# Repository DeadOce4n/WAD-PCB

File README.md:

# WearableAffectionDevice - Circuito Impreso

En este repositorio se encuentra el esquemático y el diseño de PCB para el circuito impreso
del "Dispositivo Vestible para la Transmisión de Muestras de Afecto entre Familiares Separados
Geográficamente". Desarrollado en Autodesk EAGLE.

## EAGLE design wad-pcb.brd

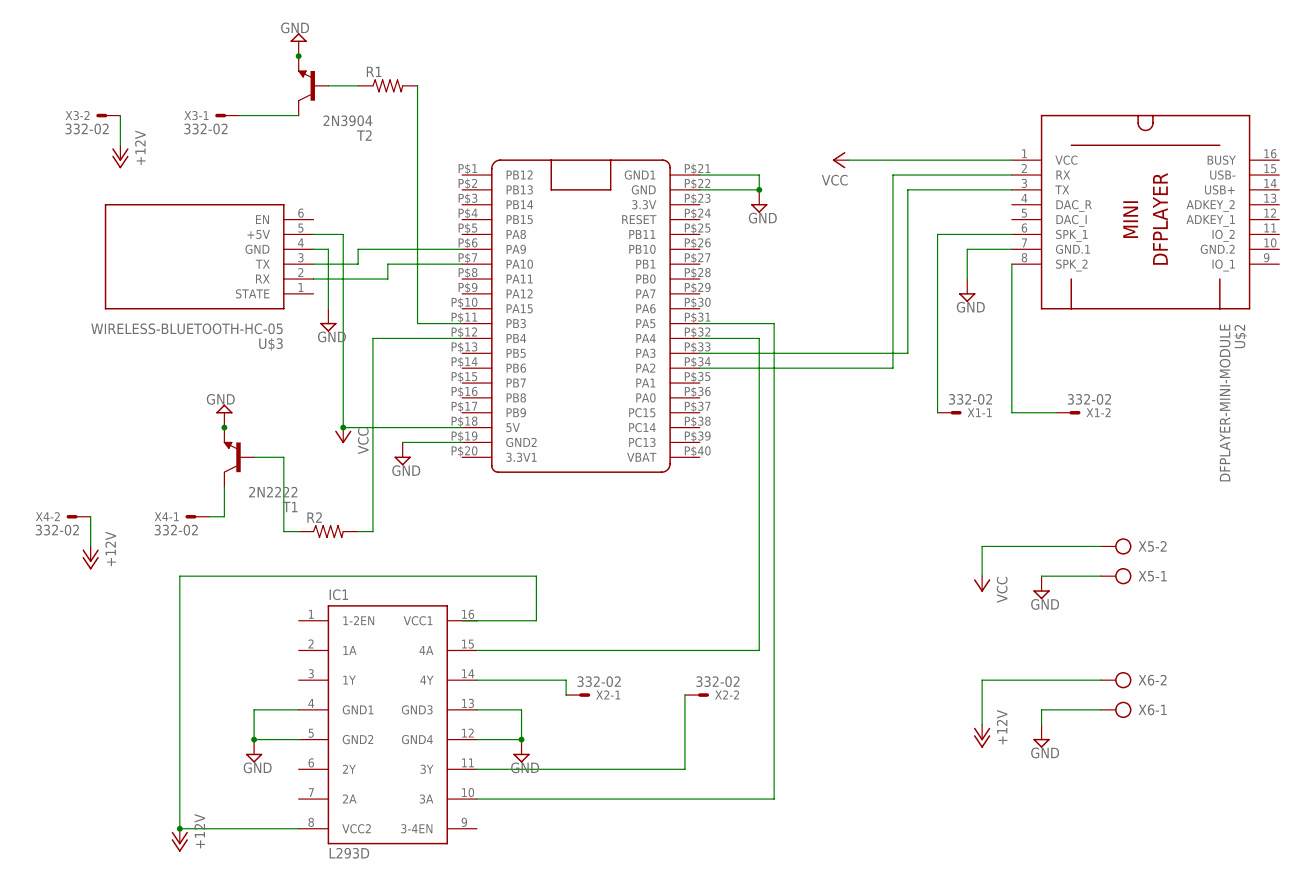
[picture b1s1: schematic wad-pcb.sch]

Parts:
IC1: L293D; DIL16
R1, R2: R-US_0204/7; 0204/7
T1: 2N2222; TO18
T2: 2N3904; TO92
U$1: BLUE_PILL
U$2: DFPLAYER-MINI-MODULE
U$3: WIRELESS-BLUETOOTH-HC-05
X1, X2, X3, X4: 332-02
X5, X6: AK500/2-H

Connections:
+12V: IC1.8 (VCC2), IC1.16 (VCC1), X3.2, X4.2, X6.2
GND: IC1.4 (GND1), IC1.5 (GND2), IC1.12 (GND4), IC1.13 (GND3), T1.1 (E), T2.3 (E), U$1.P$19 (GND2), U$1.P$21 (GND1), U$1.P$22 (GND), U$2.7 (GND.1), U$3.4 (GND), X5.1, X6.1
GND.2: U$2.10 (GND.2)
unnamed: U$1.P$6 (PA9), U$3.3 (TX)
unnamed: U$1.P$7 (PA10), U$3.2 (RX)
unnamed: R1.1, T2.2 (B)
unnamed: R1.2, U$1.P$11 (PB3)
unnamed: R2.1, T1.2 (B)
unnamed: R2.2, U$1.P$12 (PB4)
unnamed: T2.1 (C), X3.1
unnamed: T1.3 (C), X4.1
unnamed: U$1.P$34 (PA2), U$2.2 (RX)
unnamed: U$1.P$33 (PA3), U$2.3 (TX)
unnamed: U$2.6 (SPK_1), X1.1
unnamed: U$2.8 (SPK_2), X1.2
unnamed: IC1.15 (4A), U$1.P$32 (PA4)
unnamed: IC1.10 (3A), U$1.P$31 (PA5)
unnamed: IC1.14 (4Y), X2.1
unnamed: IC1.11 (3Y), X2.2
VCC: U$1.P$18 (5V), U$2.1 (VCC), U$3.5 (+5V), X5.2

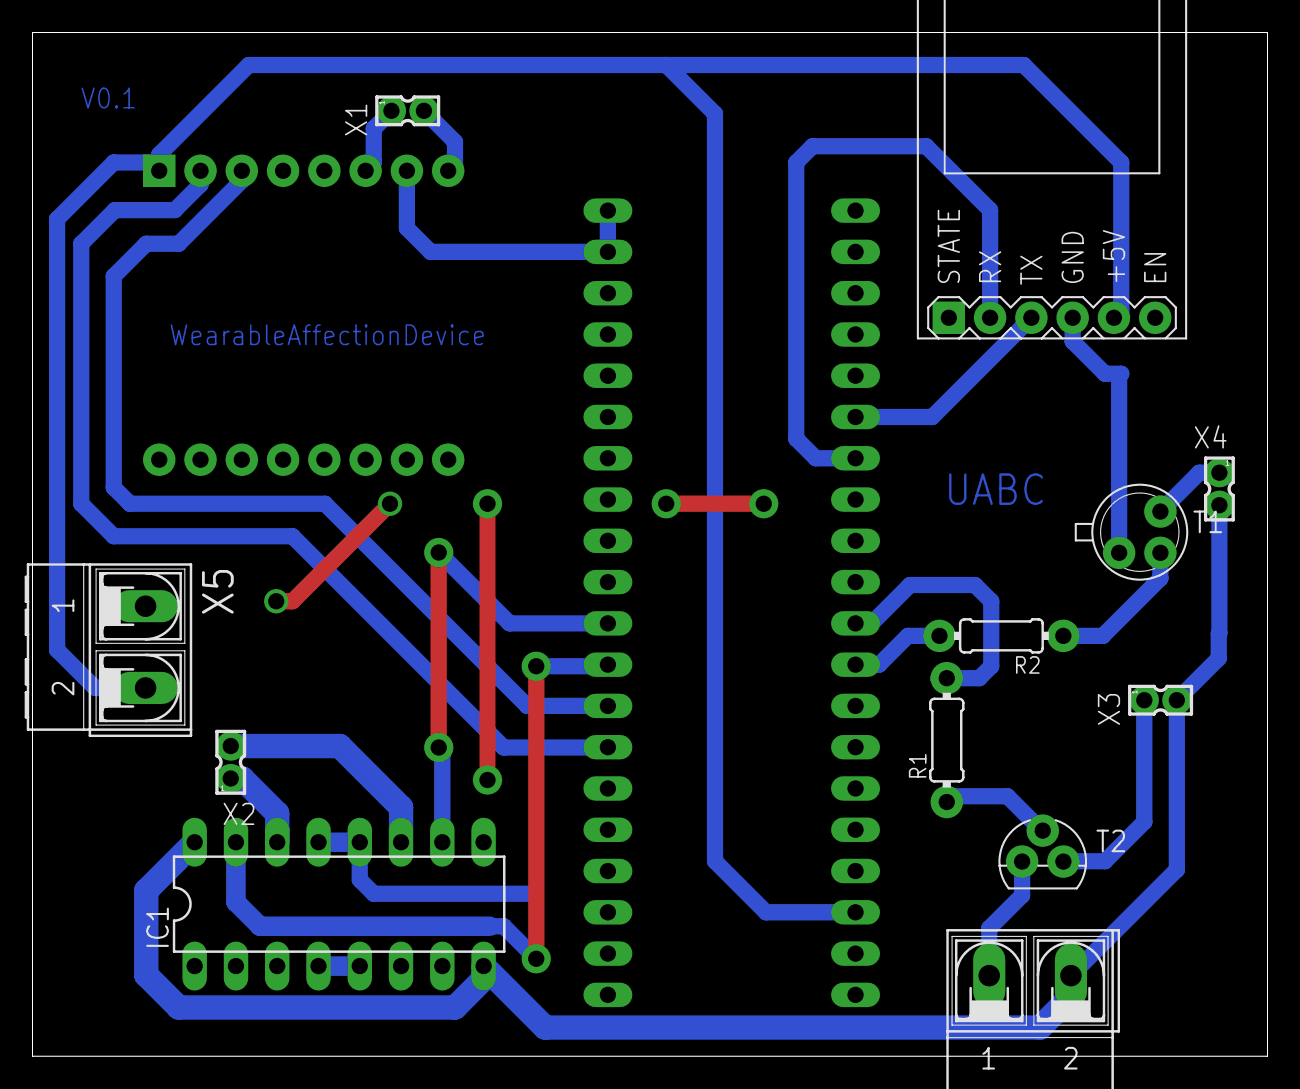
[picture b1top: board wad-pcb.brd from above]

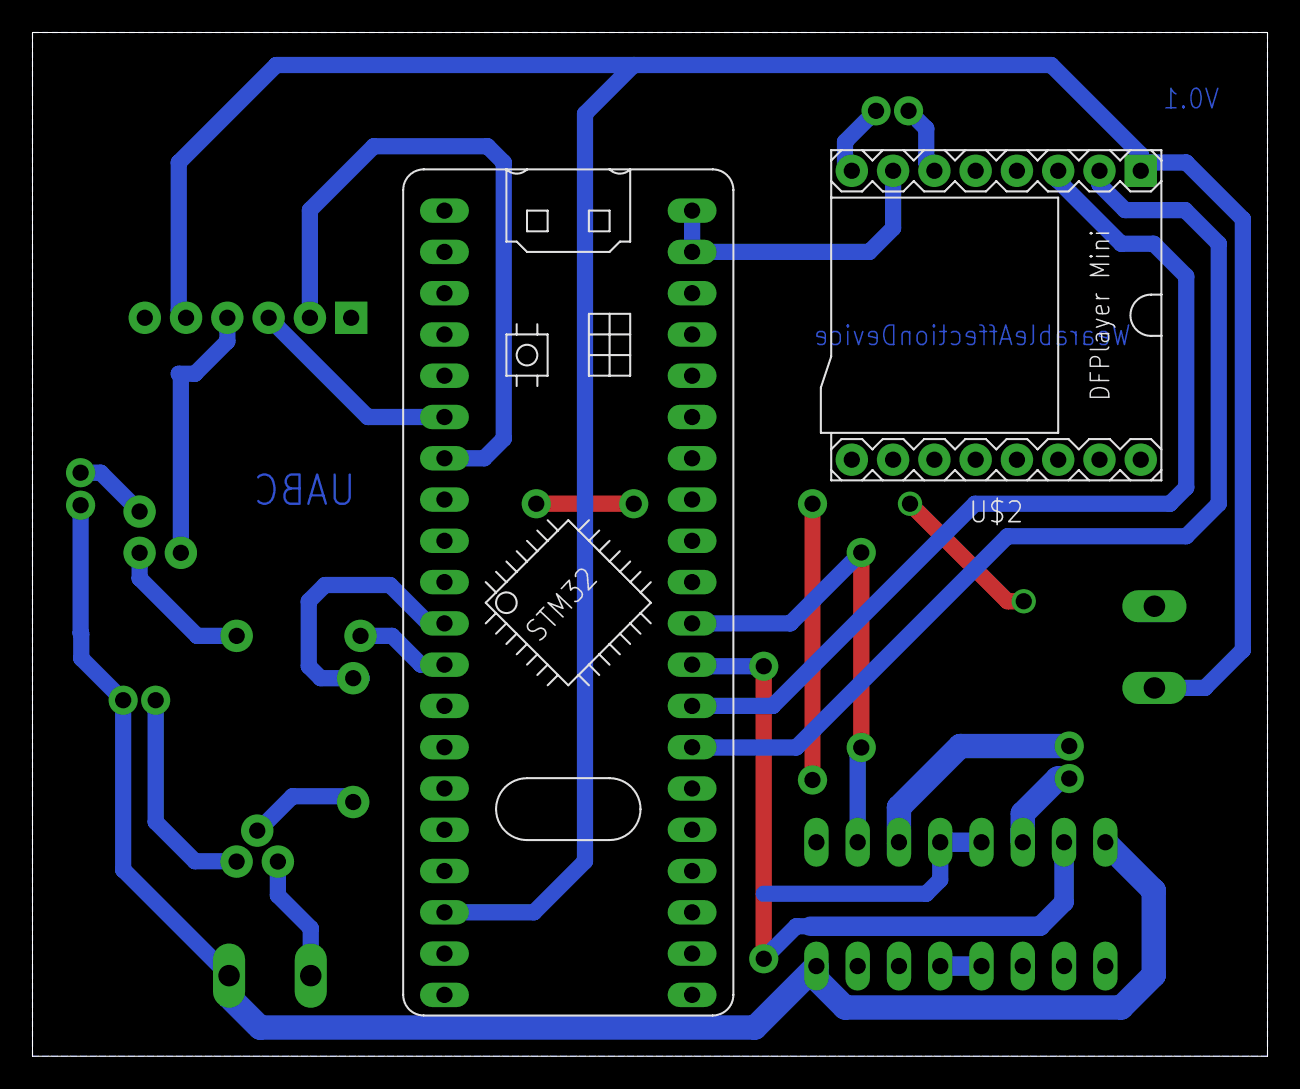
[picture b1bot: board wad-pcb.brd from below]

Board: 2 copper layers, 76.0 x 63.0 mm, 14 parts (2 on the bottom side), 19 nets.

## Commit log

2021-04-21 Primera versión

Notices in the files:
parts and their libraries:
diy-modules: Released under the Creative Commons Attribution 4.0 International License: http://creativecommons.org/licenses/by/4.0
